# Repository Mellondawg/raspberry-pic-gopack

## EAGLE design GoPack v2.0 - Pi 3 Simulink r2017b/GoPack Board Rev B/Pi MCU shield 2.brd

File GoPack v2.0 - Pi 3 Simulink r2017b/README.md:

# RaspberryPIC GoPack

The GoPack is a universal control/driver pack meant for rapid prototyping of mechatronic systems. 
It houses a **Raspberry Pi Version 3 Model B**, 16 bit dsPIC33F microcontroller, and has various analog and digital inputs and outputs. Programming the GoPack is done in **MATLAB Simulink version 2017b**, and sent wirelessly through the WLAN to the Raspberry Pi.

Last updated: 12/04/2017

## Raspberry Pi Setup: 

### 1) Installing support packages: (for starting from scratch)
The RaspberryPi boots off of an SD card with the MATLAB Support Package and operating system installed.  The MATLAB support packages are downloaded in MATLAB, and written to the Pi with a USB SD reader/writer. All remaining programming is done over wifi. The package can be found in MATLAB under the Add-Ons drop-down. Choose install from internet, choose Raspberry Pi, check all packages available for Pi, and follow the instructions. You will be guided to install your micro SD card in the USB card reader, and install the Rapberry Pi OS “Raspbian” with Matlab support packages for the appropriate Pi model. The latest version of GoPack uses Pi 3 Model B. 

When installing the Raspbian image onto the SD Card, if you follow the MATLAB Hardware Support walkthrough all the way through, then you can set up WiFi and SSH access. The Pi 3 Model B has built-in WiFi capabilities. The SSH access has pi as the user and raspberry as the default password.

This requires booting the Pi up, which is done by inserting the SD card that contains the Raspbian OS, connecting any additional peripherals (none required), and plugging in a micro USB power source.

Make note of the IP address that was assigned to the Pi 3.

### 2) Connecting to Pi with SSH from the main computer: 
Now on the PC, you need to be able to log in via SSH to have access to the Pi command prompt over the WLAN. Here you can download an executable called “Putty” to do so. http://www.chiark.greenend.org.uk/~sgtatham/putty/download.html
Save the executable in an accessible location, you will use it frequently. 
Run Putty. Click connection on the tree, and change “Seconds between keepalives” to 30 in order to keep the connection from timing out. Click Session in the tree, type in the IP address, highlight defaulty and save. You can now click open, and it will save the IP for next time. If you get a security alert, click yes. The default username and password are pi and raspberry (note the password will not show in the command window). 

If you are familiar with Bash, or any other Linux-based command lines, feel free to use those for SSH access instead.

### 3) Installing GPIO Interface Library wiringPi
The driver blocks used for PWM, ADC and Encoder inputs use the library called wiringPi www.wiringpi.com. To install wiringPi, git must first be installed. The standard image that MATLAB uses for Pi 3 already contains git.

To check if your image contains git, simply type "git" and see if you receive a help message, or an error. If you receive an error:
Boot the Pi and establish a SSH connection. Type:

`sudo apt-get install git-core`

If any errors happen, reinstall raspbian through MATLAB for the most updated copy. You can now download wiringPi. 

`git clone https://github.com/UMass-MRRL/wiringPi-GoPack.git`

Note: If you download wiringPi from its original source (git://git.drogon.net/wiringPi), that’s the wrong version. If updating wiringPi, type:
```
cd wiringPi-GoPack
git pull origin
```
Note: You must move the items within the wiringPi-GoPack directory that is created, up one level. Meaning the contents of the wiringPi-GoPack must be moved to the level where the wiringPi-GoPack directory is. This can be done by:

`sudo mv wiringPi-GoPack/** ./pi` (only type one asterisk, not two, MD formatting required me to type two here)

Shutting the Pi down:
When connected with SSH via Putty, type this to shut down safely.  

`sudo halt`

Click OK when Putty gives a fatal error, it thinks the connection has failed. Close Putty. 

## Interfacing the Raspberry Pi with the GoPack add-on board

### 1) Initializing the GoPack board
The GoPack board runs on a dsPIC33F microcontroller. A set of pins is provided for programming and debugging the microcontroller should you wish to modify the firmware. For the initial setup, ensure that the board is receiving power. 

**Note: Do not supply power through the GoPack terminals and the micro-USB connector on the Raspberry Pi at the same time.** The current iteration of the board does not have back-current protections should these 5V levels be slightly different.

With the board powered up, flash the microcontroller with the provided files using a PICkit3 or similar device. You can build, edit, and download this project to the hardware from within MPLAB, or program it directly with the provided .hex files. A bright red status LED should come on if the microcontroller is running successfully.

### 2) Interfacing with the Raspberry Pi
The only physical assembly required is mating the 40 pin male connector on the Raspberry Pi with the GoPack 40-pin female connector. The boards should stack directly on top of each other. The Raspberry Pi will receive power through this connection from the GoPack board. It is recommended to use standoffs between the boards to support the cantilevered end.

## Using GoPack with MATLAB and Simulink

### 1) Configure Simulink to run models on Raspberry Pi hardware
For Simulink to run models on the Raspberry Pi, it must be configured to run on external hardware. Enter the "Configuration Parameters" dialog and locate the "Hardware Implementation" tab. "Raspberry Pi" should be available on the "Hardware board" dropdown menu. Set the IP address for the Host name, supply the username and password for the Raspberry Pi, and set the Build directory to "/home/pi".

In the Solver tab, set the Solver options to discrete and fixed-step. Set the desired control loop sample time in the "Fixed step size (fundamental sample time)" field in seconds. (i.e. input a value of 0.001 for a 1 ms sample time).

In the Simulink model window, type "inf" for the simulation time, and set the mode to "external".

To run a model on the Raspberry Pi to view data and adjust the model in real-time, press the 'play' arrow button. To send a model to the Raspberry Pi to run independently of the host PC, click "Deploy to Hardware" on the far right of the control bar.

The Simulink blocks included in this repository use the WiringPi library to access Raspberry Pi functions not included in the standard blocks included with the Mathworks toolbox - specifically control over SPI communication.

Make sure that setBuildArgs.m is included in the active directory. This file is included in the Simulink Scripting section of this repository.

### 2) Using GoPack s-Functions to handle sensors and actuators
It is recommended that you familiarize yourself with the basics:
http://www.mathworks.com/help/supportpkg/raspberrypi/examples/getting-started-with-raspberry-pi-hardware.html

Three Simulink s-Function blocks are provided to allow the Simulink model to access sensor readings and dictate actuator outputs. 

The "inputs_to_SPI_bytes" block converts float or integer inputs into bytes for serial transfer. This primarily means motor duty cycle or voltage input. It also formats requests for readings from specific sensors.

The "SPI" block simply performs an SPI transfer of the byte vector assembled by the previous block. The output is a byte vector of requested sensor readings, and loopback confirmation of the requested outputs.

The "SPI_bytes_to_outputs" block converts the received byte vector into float or integer values for the requested sensor readings and looped-back outputs. Depending on the amount of samples the sensor is configured to perform per Simulink loop, outputs corresponding with each separate sensor reading can be a vector containing multiple samples. Filtering, chronological arrangement of this data, or averaging are left to the user to perform with standard Simulink blocks as needed.

Note that a single sample delay function is required before the input to the serial transfer subsystem made up of these three blocks. The model will form an algebraic loop and will not run if the delay is not included.

It is recommended to use the provided PID position control model for reference. It uses encoder feedback (500 counts/turn) to drive a DC motor while logging data from 5 simultaneous analog inputs. This controller was successfully tested with a Maxon EC30 motor using an ESCON 50/5 motor driver.

## Additional Information

### 1) MATLAB and Simulink Upgrade Troubleshooting
MATLAB versions are released bi-annually, and usually contain upgrades to Simulink as well. When installing this repository on a different version, it may require you to delete the "slprj" folder. This folder is created by MATLAB on execution, and houses "files generated by Simulink diagram updates and model builds." Becuase this folder had been procedurally generated using MATLAB, deleting it and allowing it to be re-generated should lead to successful execution.

If issues persist in the newer version, then we would recommend creating a new Simulink model, copying over the model that had worked in the previous iteration, and remaking the S-function blocks. All parameters needed for creation should be viewable from the older version.

Additionally, if the S-Function builder of Simulink is unable to detect the supported compiler that is being used, please ccheck out this MATLAB Answers link, which details how entering these two commands should help (they only have to be entered once, not every time you run the model): 
```
>> rtwMKCFG_out=rtwmakecfg
>> mex(['-I' rtwMKCFG_out.includePath{:}], ['-I' rtwMKCFG_out.sourcePath{:}], ['-L' rtwMKCFG_out.linkLibsObjs{:}], 'yourSFunctionName.c', 'yourSFunctionName_wrapper.c', '-lfixedpoint')
```
https://www.mathworks.com/matlabcentral/answers/92279-why-do-i-get-an-error-when-i-use-the-s-function-builder-in-64-bit-simulink-with-the-windows-sdk-7-1?s_tid=gn_loc_drop

### 2) Linux Tips
If you would like to learn more about basic Linux commands, and how they could be used to help navigate the Raspberry Pi, or gather RAM and CPU usage, please check out: 

Linux man page: https://linux.die.net/man/
Contains information about all of the Linux commands. Particularly useful are: cd, ls, mv, ssh, and top (which shows RAM usage).

htop: http://hisham.hm/htop/
An interactive process viewer for Unix that can show core utilization.

### 3) Hardware Specifications
This table is created from information available on http://socialcompare.com/en/comparison/raspberrypi-models-comparison and https://www.raspberrypi.org/

| Model         | Raspberry Pi Zero W | Pi 3 Model B       | Pi 2 Model B       |
|---------------|---------------------|--------------------|--------------------|
| Release Date  | Feb 28, 2017        | Feb 29, 2017       | Feb 1, 2015        |
| Price         | $10                 | $35                | $35                |
| SOC Type      | Broadcom BCM        | Broadcom BCM       | Broadcom BCM       |
| Core Type     | ARM1176JZF-S        | Cortex-A53 64-bit  | Cortex-A7          |
| No. of Cores  | 1                   | 4                  | 4                  |
| GPU           | VideoCore IV        | VideoCore IV       | VideoCore IV       |
| CPU Clock     | 1 GHz               | 1.2 GHz            | 900 MHz            |
| RAM           | 512 MB              | 1 GB               | 1 GB               |
| USB Ports     | Micro & micro OTG   | 4                  | 4                  |
| HDMI          | Mini                | Yes                | Yes                |
| I2C/SPI       | Yes                 | Yes                | Yes                |
| GPIO          | Yes                 | Yes                | Yes                |
| Camera        | Yes                 | Yes                | Yes                |
| SD            | microSD             | microSD            | microSD            |
| Wi-Fi         | 802.11n             | 802.11n            | No                 |
| Bluetooth     | 4.1                 | 4.1 LE             | No                 |
| Ethernet Port | No                  | Yes                | Yes                |
| Height        | 1.18 in (30mm)      | 2.22 in (56.5 mm)  | 3.37 in (85.6 mm)  |
| Width         | 2.55 in (65 mm)     | 3.37 in (85.6 mm)  | 2.22 in (56.5 mm)  |
| Depth         | 0.19685 in (5 mm)   | 0.66929 in (17 mm) | 0.66929 in (17 mm) |
| Weight        | 0.31746 oz. (9 g)   | 1.58 oz. (45 g)    | 1.58 oz. (45 g)    |

To gather information about the RAM and CPU usage, check out the top and htop Linux commands.

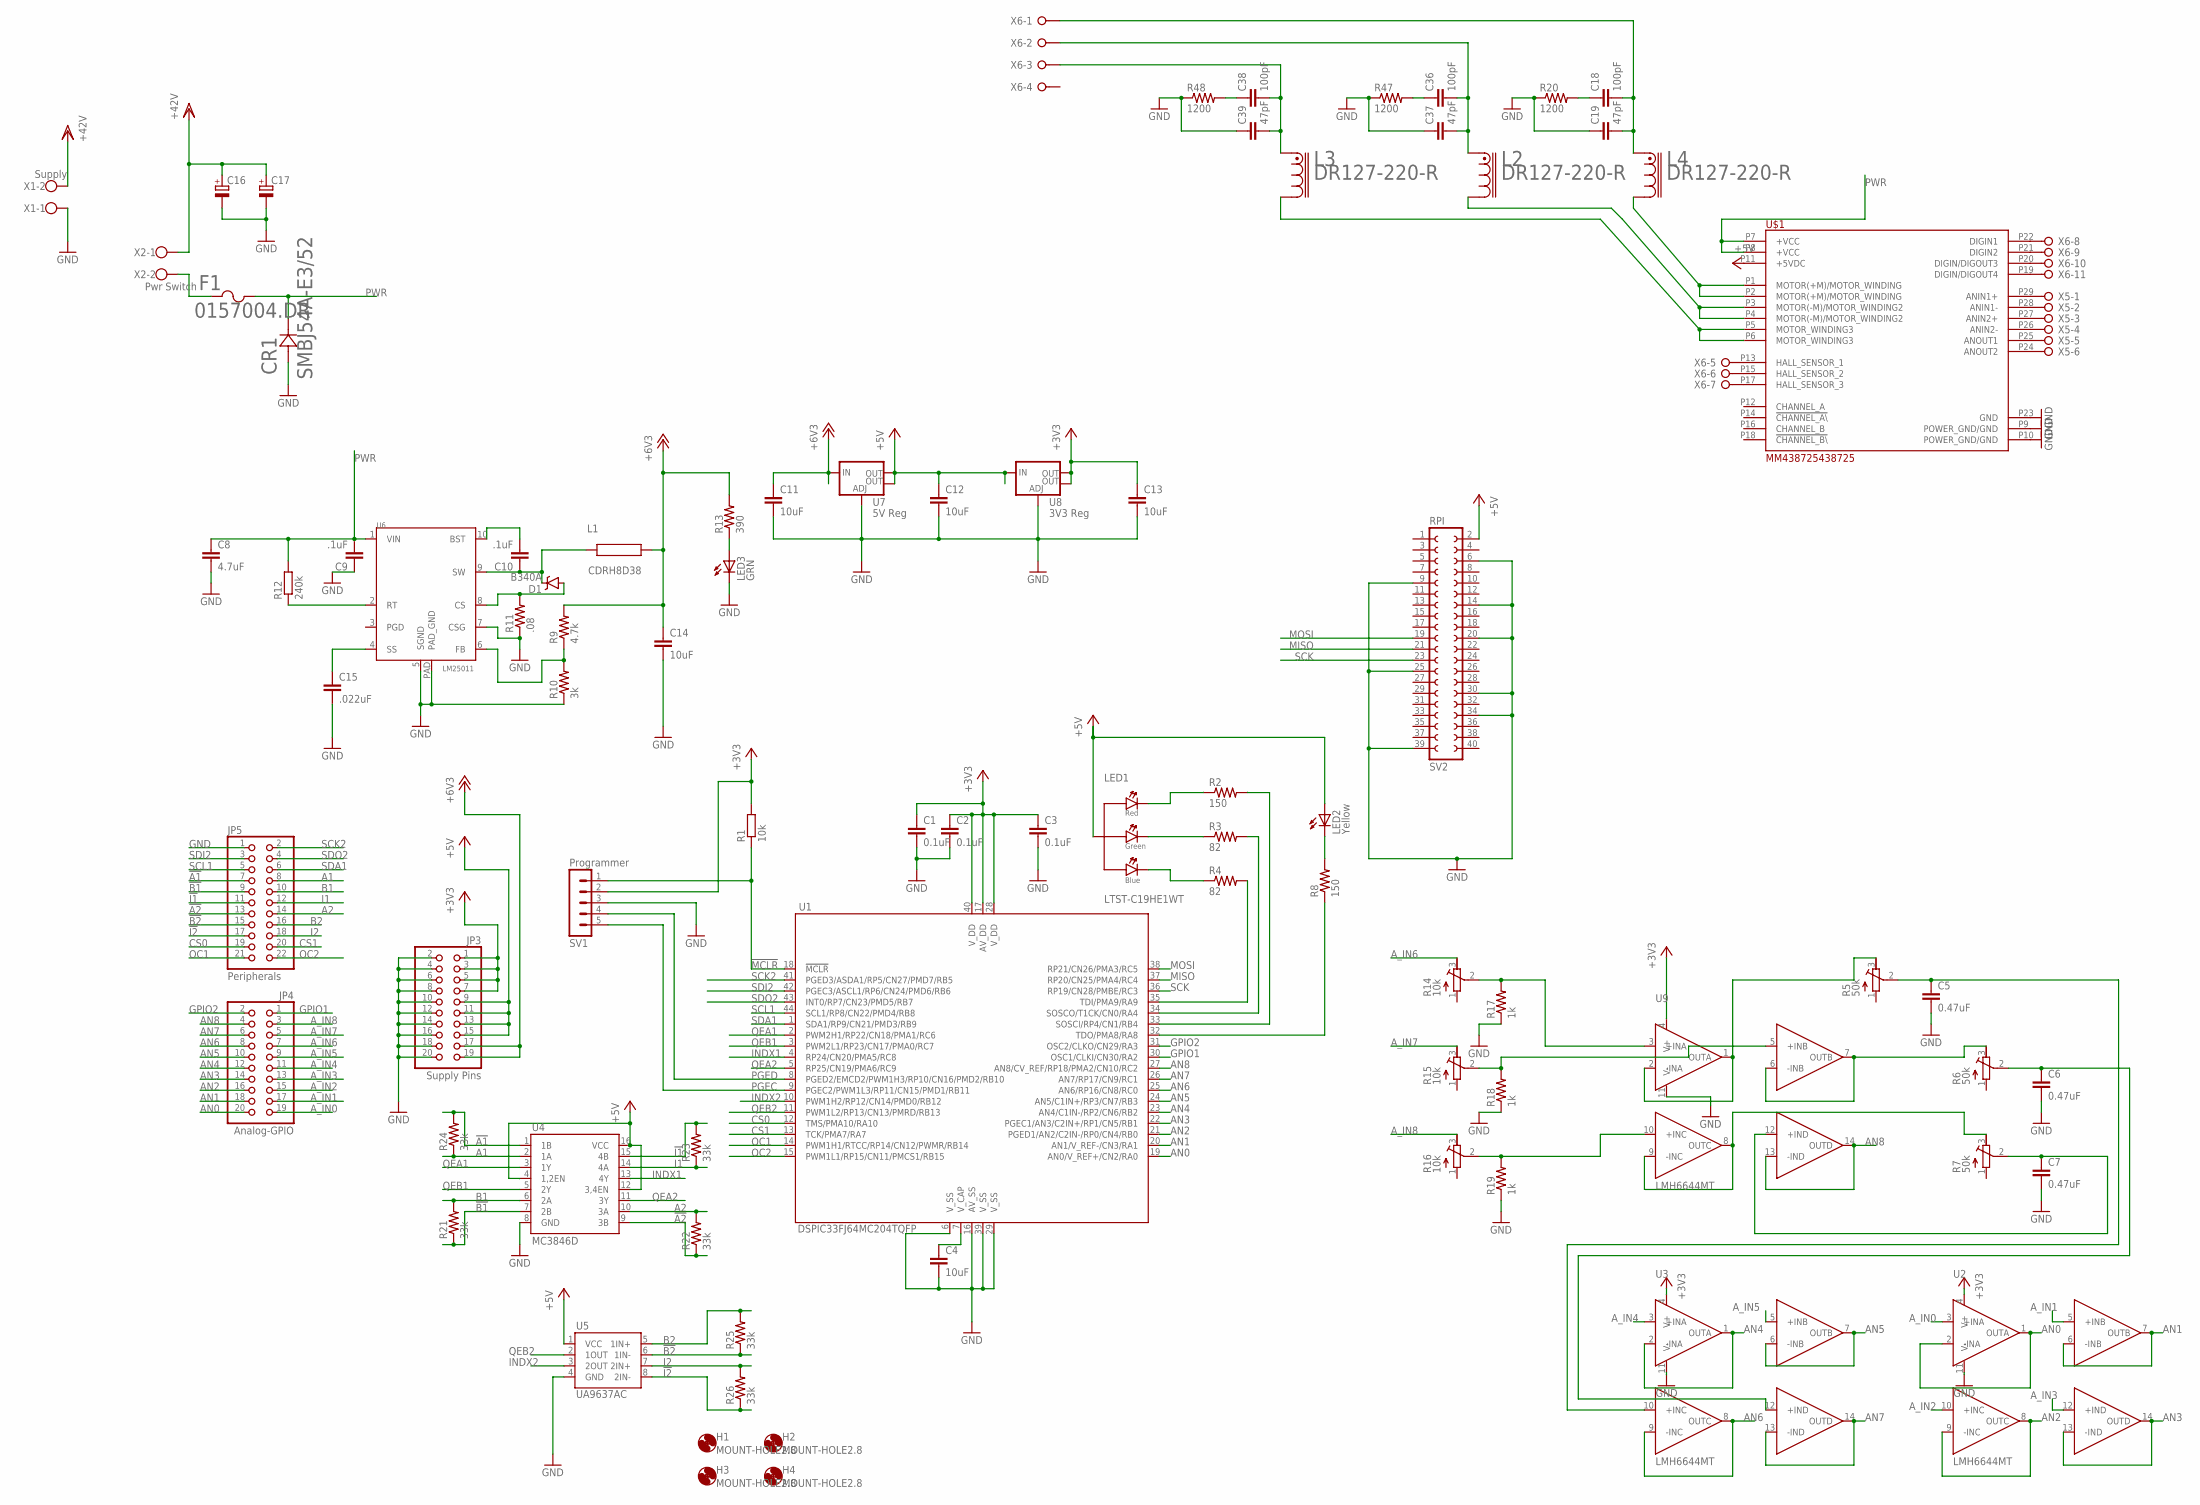
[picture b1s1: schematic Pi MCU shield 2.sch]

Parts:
C1, C2, C3: 0.1uF; C0603
C4, C14: 10uF; C1206
C5, C6, C7: 0.47uF; C0603
C8: 4.7uF; C1210
C9, C10: .1uF; 0603-CAP
C11, C12, C13: 10uF; C0805
C15: .022uF; 0603-CAP
C16, C17: CPOL-EUE5-13; E5-13
C18, C36, C38: 100pF; 0603-CAP
C19, C37, C39: 47pF; 0603-CAP
CR1: SMBJ54A-E3/52; DIODE_DO-214AC
D1: B340A; SMA-DIODE
F1: 0157004.DR; 0157SERIES
H1, H2, H3, H4: MOUNT-HOLE2.8; 2,8
JP3: Supply Pins; 2X10
JP4: Analog-GPIO; 2X10
JP5: Peripherals; 2X11
L1: CDRH8D38
L2, L3, L4: DR127-220-R; DR127
LED1: LTST-C19HE1WT; 0606
LED2: Yellow; SML0603
LED3: GRN; CHIP-LED0805
R1: 10k; R0805
R2, R8: 150; R0603
R3, R4: 82; R0603
R5, R6, R7: 50k; RTRIM3224J
R9: 4.7k; 0603-RES
R10: 3k; 0603-RES
R11: .08; 0603-RES
R12: 240k; R0805
R13: 390; 0603-RES
R14, R15, R16: 10k; RTRIM3224J
R17, R18, R19: 1k; R0603
R20, R47, R48: 1200; R0603
R21, R22, R23, R24, R25, R26: 33k; R0603
SV1: Programmer; MA05-1
SV2: RPI; FE20-2
U1: DSPIC33FJ64MC204TQFP; TQFP44
U2, U3, U9: LMH6644MT; TSSOP14
U4: MC3846D; SO-16
U5: UA9637AC; SO-08
U6: LM25011; HVSS0P-10
U7: 5V Reg; SOT223
U8: 3V3 Reg; SOT223
U$1: MM438725438725; MAX_MOT_438725
X1: Supply; W237-102
X2: Pwr Switch; W237-102
X5: W237-06P; W237-6P
X6: W237-11P

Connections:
!A1: JP5.7, R24.2, U4.1 (1B)
!A2: JP5.13, R22.1, U4.9 (3B)
!B1: JP5.9, R21.1, U4.7 (2B)
!B2: JP5.15, R25.1, U5.6 (1IN-)
!I1: JP5.11, R23.2, U4.15 (4B)
!I2: JP5.17, R26.1, U5.8 (2IN-)
!MCLR: R1.1, SV1.1, U1.18 (!MCLR)
+3V3: C1.1, C2.1, C3.1, C13.1, JP3.1, JP3.3, JP3.5, JP3.7, R1.2, SV1.2, U1.17 (AV_DD), U1.28 (V_DD), U1.40 (V_DD), U2.4 (V+), U3.4 (V+), U8.2 (OUT), U8.4 (OUT), U9.4 (V+)
+5V: C12.1, JP3.9, JP3.11, JP3.13, JP3.15, LED1.4 (ANODE), LED2.A, SV2.2, U4.4 (1,2EN), U4.12 (3,4EN), U4.16 (VCC), U5.1 (VCC), U7.2 (OUT), U7.4 (OUT), U8.3 (IN), U$1.P11 (+5VDC)
+6V3: C11.1, C14.1, JP3.17, JP3.19, L1.P$2 (2), R9.2, R13.2, U7.3 (IN)
A1: JP5.8, R24.1, U4.2 (1A)
A2: JP5.14, R22.2, U4.10 (3A)
AN0: JP4.20, U1.19 (AN0/V_REF+/CN2/RA0), U2.1 (OUTA), U2.2 (-INA)
AN1: JP4.18, U1.20 (AN1/V_REF-/CN3/RA1), U2.6 (-INB), U2.7 (OUTB)
AN2: JP4.16, U1.21 (PGED1/AN2/C2IN-/RP0/CN4/RB0), U2.8 (OUTC), U2.9 (-INC)
AN3: JP4.14, U1.22 (PGEC1/AN3/C2IN+/RP1/CN5/RB1), U2.13 (-IND), U2.14 (OUTD)
AN4: JP4.12, U1.23 (AN4/C1IN-/RP2/CN6/RB2), U3.1 (OUTA), U3.2 (-INA)
AN5: JP4.10, U1.24 (AN5/C1IN+/RP3/CN7/RB3), U3.6 (-INB), U3.7 (OUTB)
AN6: JP4.8, U1.25 (AN6/RP16/CN8/RC0), U3.8 (OUTC), U3.9 (-INC)
AN7: JP4.6, U1.26 (AN7/RP17/CN9/RC1), U3.13 (-IND), U3.14 (OUTD)
AN8: JP4.4, U1.27 (AN8/CV_REF/RP18/PMA2/CN10/RC2), U9.13 (-IND), U9.14 (OUTD)
A_IN0: JP4.19, U2.3 (+INA)
A_IN1: JP4.17, U2.5 (+INB)
A_IN2: JP4.15, U2.10 (+INC)
A_IN3: JP4.13, U2.12 (+IND)
A_IN4: JP4.11, U3.3 (+INA)
A_IN5: JP4.9, U3.5 (+INB)
A_IN6: JP4.7, R14.3 (E)
A_IN7: JP4.5, R15.3 (E)
A_IN8: JP4.3, R16.3 (E)
B1: JP5.10, R21.2, U4.6 (2A)
B2: JP5.16, R25.2, U5.5 (1IN+)
BLUE: LED1.2 (G_CATHODE), R3.1
CS0: JP5.19, U1.12 (TMS/PMA10/RA10)
CS1: JP5.20, U1.13 (TCK/PMA7/RA7)
GND: C1.2, C2.2, C3.2, C4.2, C5.2, C6.2, C7.2, C8.2, C9.1, C11.2, C12.2, C13.2, C14.2, C15.2, C16.-, C17.-, C19.1, C37.1, C39.1, CR1.2 (21), JP3.2, JP3.4, JP3.6, JP3.8, JP3.10, JP3.12, JP3.14, JP3.16, JP3.18, JP3.20, JP5.1, LED3.C, R10.1, R11.1, R17.1, R18.1, R19.1, R20.1, R47.1, R48.1, SV1.3, SV2.6, SV2.9, SV2.14, SV2.20, SV2.25, SV2.30, SV2.34, SV2.39, U1.6 (V_SS), U1.16 (AV_SS), U1.29 (V_SS), U1.39 (V_SS), U2.11 (V-), U3.11 (V-), U4.8 (GND), U5.4 (GND), U6.5 (SGND), U6.7 (CSG), U6.PAD (PAD_GND), U7.1 (ADJ), U8.1 (ADJ), U9.11 (V-), U$1.P9 (POWER_GND/GND), U$1.P10 (POWER_GND/GND), U$1.P23 (GND), X1.1
GPIO1: JP4.1, U1.30 (OSC1/CLKI/CN30/RA2)
GPIO2: JP4.2, U1.31 (OSC2/CLKO/CN29/RA3)
GREEN: LED1.3 (B_CATHODE), R4.1
I1: JP5.12, R23.1, U4.14 (4A)
I2: JP5.18, R26.2, U5.7 (2IN+)
INDX1: U1.4 (RP24/CN20/PMA5/RC8), U4.13 (4Y)
INDX2: U1.10 (PWM1H2/RP12/CN14/PMD0/RB12), U5.3 (2OUT)
MISO: SV2.21, U1.37 (RP20/CN25/PMA4/RC4)
MOSI: SV2.19, U1.38 (RP21/CN26/PMA3/RC5)
unnamed: R15.2 (S), R18.2, U9.5 (+INB)
unnamed: C4.1, U1.7 (V_CAP)
unnamed: C7.1, R7.2 (S), U9.12 (+IND)
unnamed: C5.1, R5.2 (S), U3.10 (+INC)
unnamed: C18.2, C19.2, L4.1, X6.1
unnamed: L4.2, U$1.P1 (MOTOR(+M)/MOTOR_WINDING), U$1.P2 (MOTOR(+M)/MOTOR_WINDING)
unnamed: U$1.P13 (HALL_SENSOR_1), X6.5
unnamed: R14.2 (S), R17.2, U9.3 (+INA)
unnamed: C18.1, R20.2
unnamed: U$1.P15 (HALL_SENSOR_2), X6.6
unnamed: U$1.P17 (HALL_SENSOR_3), X6.7
unnamed: U$1.P22 (DIGIN1), X6.8
unnamed: U$1.P21 (DIGIN2), X6.9
unnamed: R6.3 (E), U9.6 (-INB), U9.7 (OUTB)
unnamed: U$1.P20 (DIGIN/DIGOUT3), X6.10
unnamed: R7.3 (E), U9.8 (OUTC), U9.9 (-INC)
unnamed: U$1.P19 (DIGIN/DIGOUT4), X6.11
unnamed: U$1.P29 (ANIN1+), X5.1
unnamed: U$1.P28 (ANIN1-), X5.2
unnamed: U$1.P27 (ANIN2+), X5.3
unnamed: LED3.A, R13.1
unnamed: C36.2, C37.2, L2.1, X6.2
unnamed: LED2.C, R8.2
unnamed: U$1.P26 (ANIN2-), X5.4
unnamed: U$1.P25 (ANOUT1), X5.5
unnamed: R4.2, U1.35 (TDI/PMA9/RA9)
unnamed: R3.2, U1.34 (SOSCO/T1CK/CN0/RA4)
unnamed: R2.2, U1.33 (SOSCI/RP4/CN1/RB4)
unnamed: R16.2 (S), R19.2, U9.10 (+INC)
unnamed: R8.1, U1.32 (TDO/PMA8/RA8)
unnamed: C10.1, D1.C, L1.P$1 (1), U6.9 (SW)
unnamed: U$1.P24 (ANOUT2), X5.6
unnamed: R9.1, R10.2, U6.6 (FB)
unnamed: R12.1, U6.2 (RT)
unnamed: C15.1, U6.4 (SS)
unnamed: D1.A, R11.2, U6.8 (CS)
unnamed: C10.2, U6.10 (BST)
unnamed: C36.1, R47.2
unnamed: R5.3 (E), U9.1 (OUTA), U9.2 (-INA)
unnamed: C6.1, R6.2 (S), U3.12 (+IND)
unnamed: C38.2, C39.2, L3.1, X6.3
unnamed: C38.1, R48.2
unnamed: L2.2, U$1.P3 (MOTOR(-M)/MOTOR_WINDING2), U$1.P4 (MOTOR(-M)/MOTOR_WINDING2)
unnamed: L3.2, U$1.P5 (MOTOR_WINDING3), U$1.P6 (MOTOR_WINDING3)
OC1: JP5.21, U1.14 (PWM1H1/RTCC/RP14/CN12/PWMR/RB14)
OC2: JP5.22, U1.15 (PWM1L1/RP15/CN11/PMCS1/RB15)
PGEC: SV1.5, U1.9 (PGEC2/PWM1L3/RP11/CN15/PMD1/RB11)
PGED: SV1.4, U1.8 (PGED2/EMCD2/PWM1H3/RP10/CN16/PMD2/RB10)
PWR: C8.1, C9.2, CR1.1 (12), F1.2, R12.2, U6.1 (VIN), U$1.P7 (+VCC), U$1.P8 (+VCC)
PWR-PREFUSE: F1.1, X2.2
QEA1: U1.2 (PWM2H1/RP22/CN18/PMA1/RC6), U4.3 (1Y)
QEA2: U1.5 (RP25/CN19/PMA6/RC9), U4.11 (3Y)
QEB1: U1.3 (PWM2L1/RP23/CN17/PMA0/RC7), U4.5 (2Y)
QEB2: U1.11 (PWM1L2/RP13/CN13/PMRD/RB13), U5.2 (1OUT)
RED: LED1.1 (R_CATHODE), R2.1
SCK: SV2.23, U1.36 (RP19/CN28/PMBE/RC3)
SCK2: JP5.2, U1.41 (PGED3/ASDA1/RP5/CN27/PMD7/RB5)
SCL1: JP5.5, U1.44 (SCL1/RP8/CN22/PMD4/RB8)
SDA1: JP5.6, U1.1 (SDA1/RP9/CN21/PMD3/RB9)
SDI2: JP5.3, U1.42 (PGEC3/ASCL1/RP6/CN24/PMD6/RB6)
SDO2: JP5.4, U1.43 (INT0/RP7/CN23/PMD5/RB7)
VDD: C16.+, C17.+, X1.2, X2.1

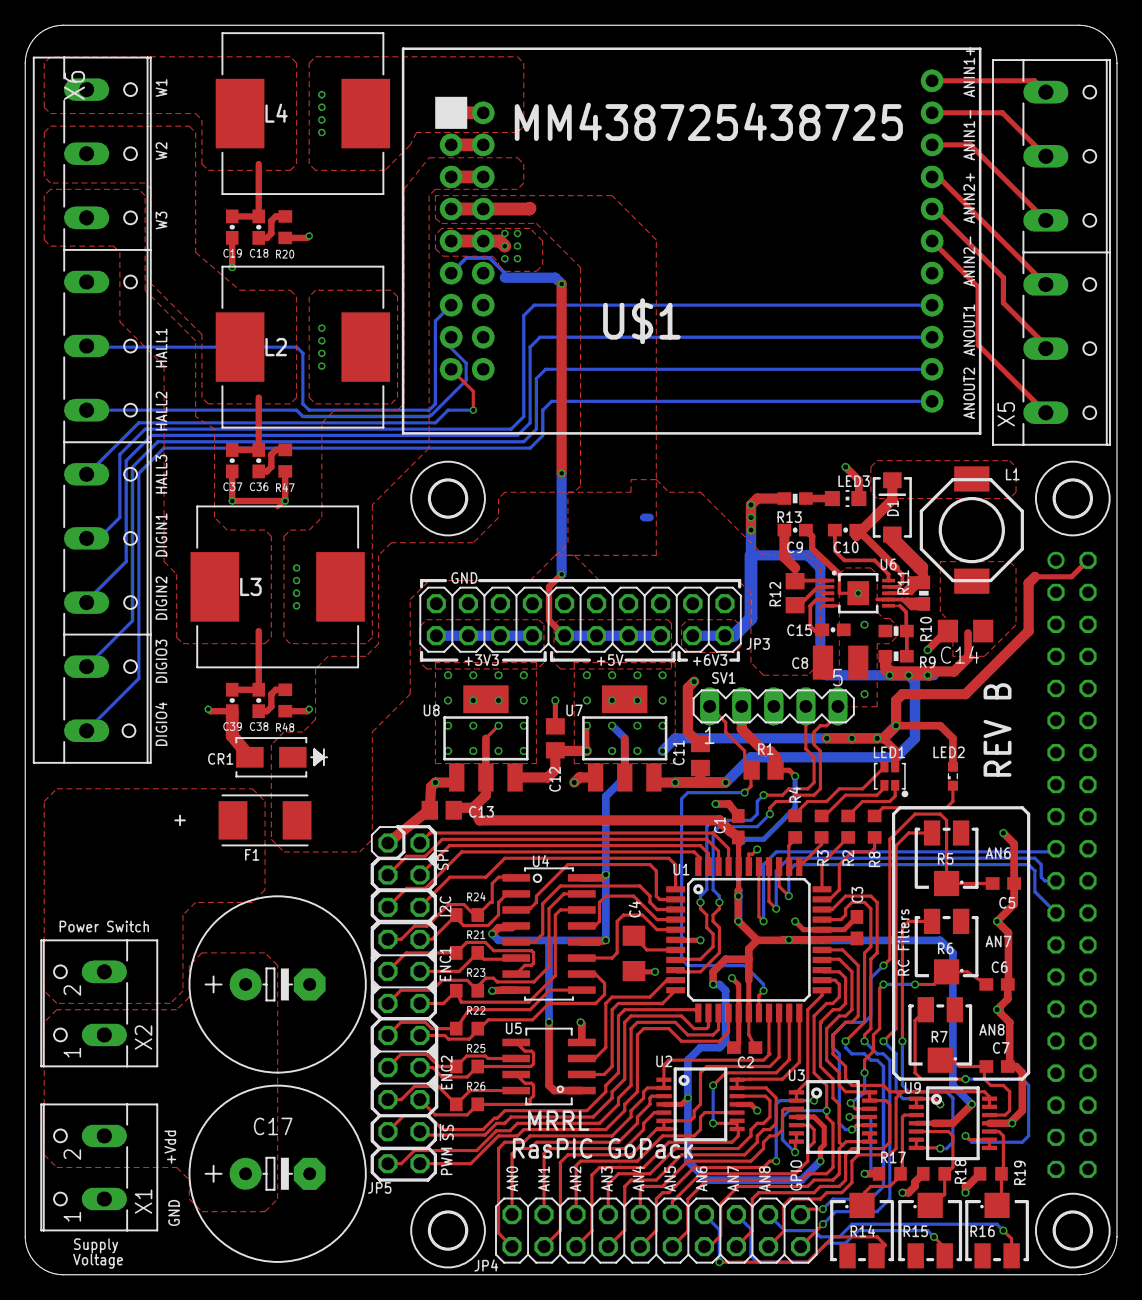
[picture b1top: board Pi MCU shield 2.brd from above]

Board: 2 copper layers, 86.5 x 99.0 mm, 84 parts (1 on the bottom side), 107 nets.

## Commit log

2018-01-15 ReadMe work
2018-01-16 README Editing
2018-01-17 Added switch model
2018-05-03 Final commit containing switching
2018-05-03 Added New Board Files
2018-05-03 Adding Board Files
2018-05-04 Added more accurate pricing
2018-05-04 Added link to motor module
2018-05-04 Directory name change

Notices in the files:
parts and their libraries:
SparkFun-Capacitors: Licensing: Creative Commons ShareAlike 4.0 International - https://creativecommons.org/licenses/by-sa/4.0
